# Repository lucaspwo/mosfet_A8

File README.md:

# Placa MOSFET para Anet A8
Baseado na placa MOSFET de [c4sfer no Thingiverse](https://www.thingiverse.com/thing:2059114)

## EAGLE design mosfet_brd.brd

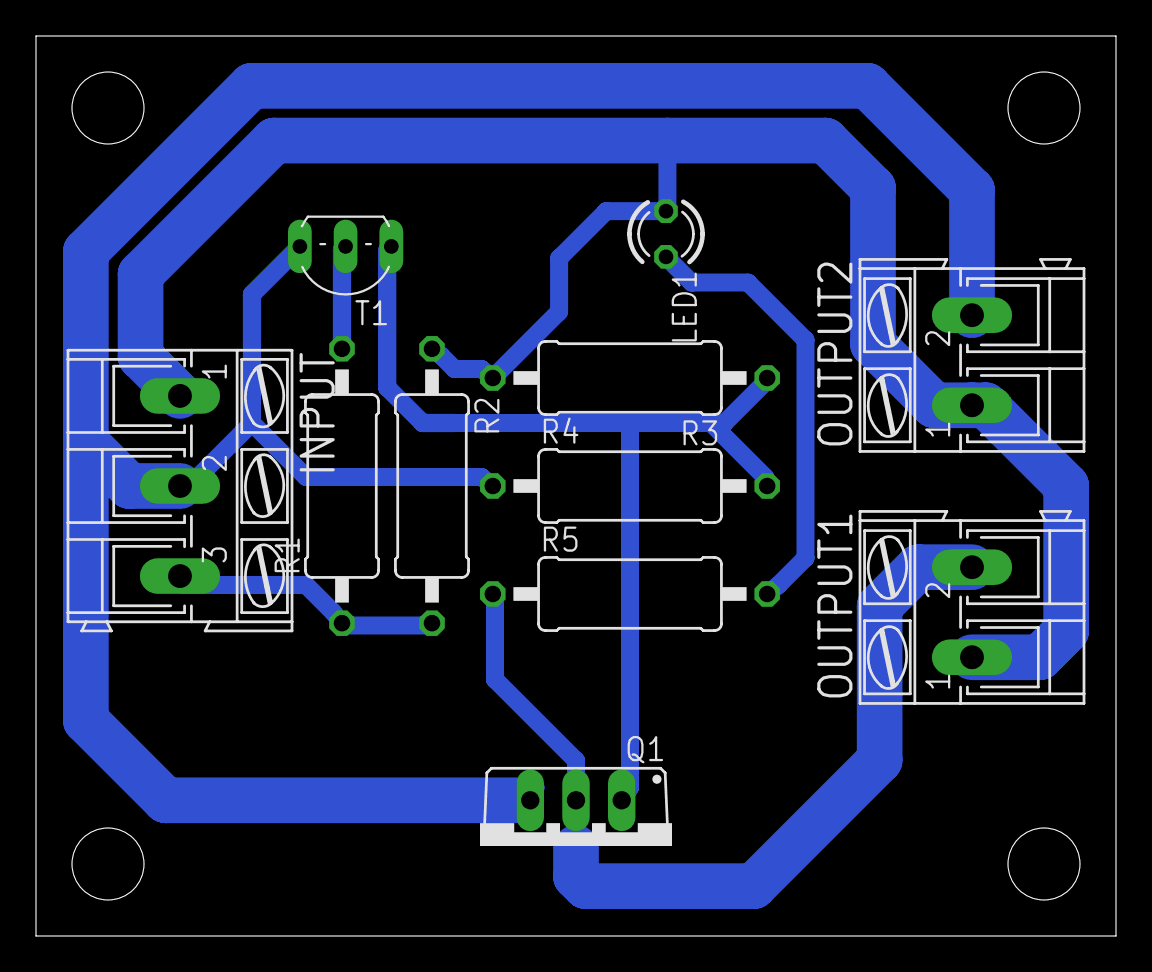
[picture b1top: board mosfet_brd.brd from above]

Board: 2 copper layers, 60.0 x 50.0 mm, 11 parts (0 on the bottom side), 7 nets.

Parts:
INPUT: AK300/3
LED1: LED3MM
OUTPUT1, OUTPUT2: AK300/2
Q1: IRF2807; TO220BV
R1: 1k; 0411/15
R2: 2k2; 0411/15
R3: 20k; 0411/15
R4: 100k; 0411/15
R5: 220R; 0411/15
T1: BC547; TO92-EBC

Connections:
GND: INPUT.2, OUTPUT2.2, Q1.S, R4.1, T1.E
GND-O: OUTPUT1.2, Q1.D, R5.1
unnamed: R1.2, T1.B
unnamed: Q1.G, R3.1, R4.2, T1.C
unnamed: LED1.K, R5.2
SIGNAL: INPUT.3, R1.1, R2.2
VCC: INPUT.1, LED1.A, OUTPUT1.1, OUTPUT2.1, R2.1, R3.2

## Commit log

2018-05-31 Adc. borne p/ segunda placa
2018-05-31 Pasta reorganizada
2018-06-05 Peq mudanças
